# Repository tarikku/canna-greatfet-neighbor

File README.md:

# Canna - a CAN access neighbor
## for GreatFET

Extends GreatFET with access to two CAN channels over TJA1042T-3 CAN transceivers

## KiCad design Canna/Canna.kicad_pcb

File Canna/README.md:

# Canna - a CAN access neighbor
## for GreatFET
### PCB info

- CAN0_TD: P3_2
- CAN0_RD: P3_1
- CAN0_STB: P2_11

- CAN1_TD: P1_17
- CAN1_RD: P1_18
- CAN1_STB: P1_0

### Canna rev1 assembled PCB

### ToDo list
- [ ] Make Canna more neighborly by changing CAN transceiver control from direct GPIO to an I2C expander (with at least 6 controllable digital I/Os)
- [ ] Remove the EEPROM as it is not needed
- [ ] Make PCB modular, so that CAN transceivers can be swapped out e.g. by placing them on pluggable daughter boards
- [ ] Find a Canna image (outline?) suitable for use as silkscreen PCB art

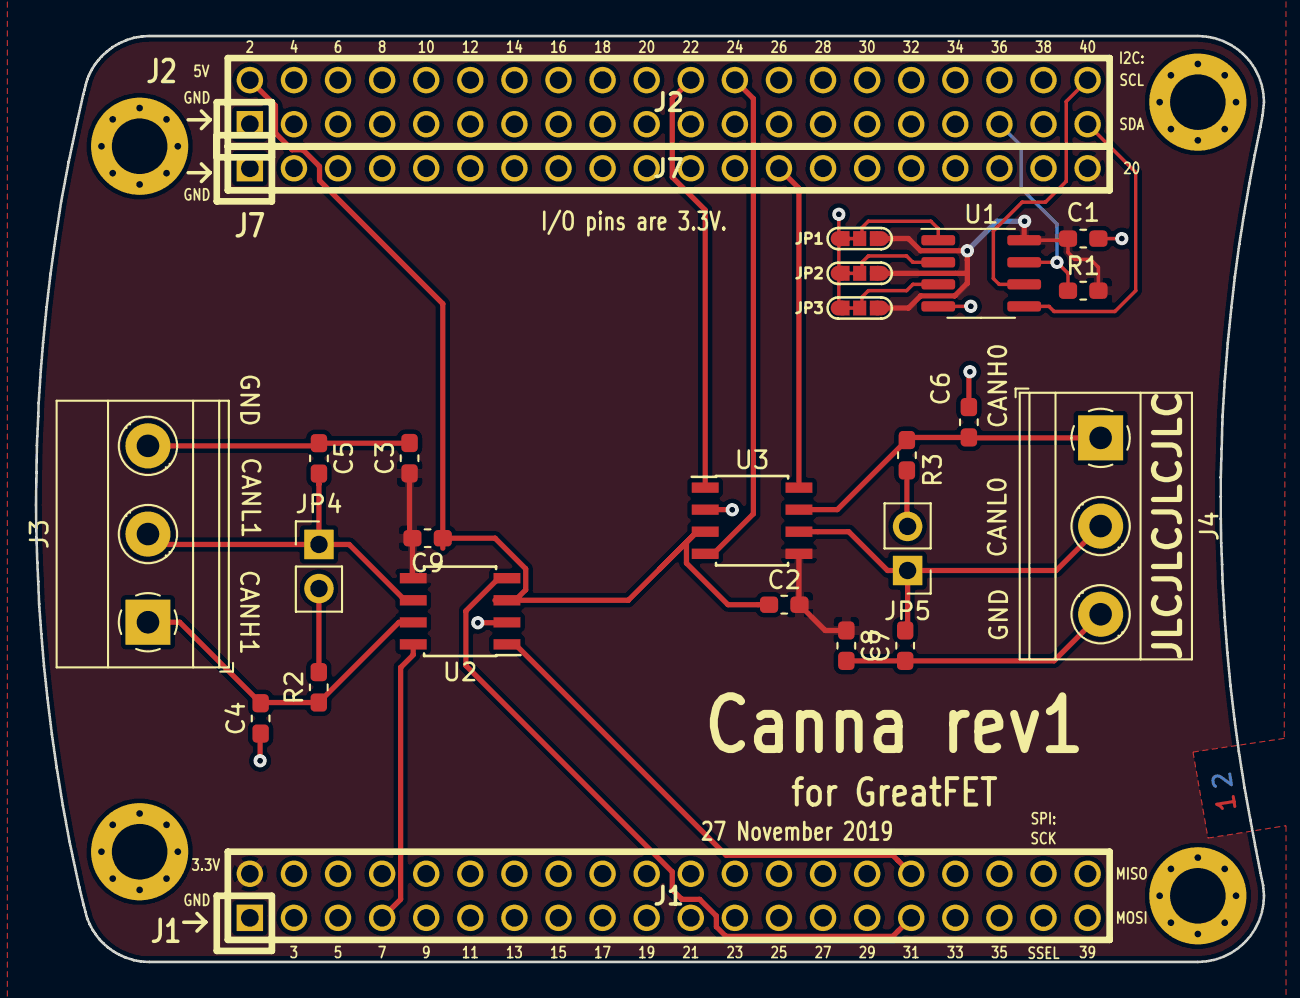
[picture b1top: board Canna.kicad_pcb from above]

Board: 2 copper layers, 70.7 x 53.3 mm, 29 parts (0 on the bottom side), 21 nets.

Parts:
C1, C2, C9: 100nF; C_0603_1608Metric_Pad1.05x0.95mm_HandSolder
C3, C8: 47nF; C_0603_1608Metric_Pad1.05x0.95mm_HandSolder
C4, C5, C6, C7: 100pF; C_0603_1608Metric_Pad1.05x0.95mm_HandSolder
J1: NEIGHBOR1; HEADER-2x20
J2: NEIGHBOR2; HEADER-2x20
J3, J4: Screw_Terminal_01x03; TerminalBlock_Phoenix_MKDS-1,5-3-5.08_1x03_P5.08mm_Horizont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
J7: BONUS_ROW; HEADER-1x20
JP1, JP2, JP3: Jumper_3_Bridged12; 0603-JUMPER-3-BRIDGED12
JP4, JP5: Jumper_2_Bridged; PinHeader_1x02_P2.54mm_Vertical
MH1, MH2, MH3, MH4: MOUNTING_HOLE; HOLE126MIL-COPPER
R1: 10k; R_0603_1608Metric_Pad1.05x0.95mm_HandSolder
R2, R3: 120Ohm; R_0603_1608Metric_Pad1.05x0.95mm_HandSolder
U1: M24C02-FMN6TP; SOIC-8_3.9x4.9mm_P1.27mm
U2, U3: TJA1042T-3; SOIC-8_3.9x4.9mm_P1.27mm

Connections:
+5V: C2.1, C9.1, J2.2, U2.3, U3.3
/CANH0: C6.2, J4.1, R3.1, U3.7
/CANH1: C4.2, J3.1, R2.1, U2.7
/CANL0: C7.2, J4.2, JP5.1, U3.6
/CANL1: C5.2, J3.2, JP4.1, U2.6
/E0: JP1.2, U1.1
/E1: JP2.2, U1.2
/E2: JP3.2, U1.3
/I2C0_SCL: J2.40, U1.6
/I2C0_SDA: J2.39, U1.5
/P1_0: J1.7, U2.8
/P1_17: J1.32, U2.1
/P1_18: J1.31, U2.4
/P2_1: J2.35, R1.1, U1.7
/P2_11: J7.13, U3.8
/P3_1: J2.24, U3.4
/P3_2: J2.22, U3.1
GND: C1.1, C3.2, C4.1, C5.1, C6.1, C7.1, C8.2, J1.1, J2.1, J3.3, J4.3, J7.1, J7.19, JP1.1, JP2.1, JP3.1, MH1.1, MH2.1, MH3.1, MH4.1, U1.4, U2.2, U3.2
unnamed: JP4.2, R2.2
unnamed: JP5.2, R3.2
VCC: C1.2, C2.2, C3.1, C8.1, C9.2, J1.2, J7.20, JP1.3, JP2.3, JP3.3, R1.2, U1.8, U2.5, U3.5

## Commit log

2019-11-25 Add Canna KiCAD project
    Add the KiCAD project for Canna from the 2 layer GreatFET neighbor template
2019-11-26 Add 2 CAN channels
2019-11-27 Finish rev1
2019-12-04 Update rev1 for fab
2019-12-04 Update files sent to fab
2020-01-19 Add Canna image
    Add image of the first assembled Canna rev1 PCB
2020-01-19 Update README.md
    Improve layout
